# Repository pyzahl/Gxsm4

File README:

ATTENTION:

THIS IS A BETA VERSION AND WORK IN PROGRESS of Gxsm4 ported to GTK4.
See details of pending / not functional parts below in section 3.
(C) PyZahl 2021-12-31

1. General Information
======================

GXSM -- Gnome X Scanning Microscopy: A multi-channel image and
vector-probe data acquisition and visualization system designed for
SPM techniques (STM,AFM..), but also SPA-LEED. A plug-in interface
allows any user add-on data-processing and special hardware and
instrument support.

Based on several hardware options it supports a commercially available
DSP hardware and provided also Open Source Code for all the low level
signal processing tasks and instrument controls in a most flexible and
adaptable manner.

All latest stable software is available
via SVN (Gxsm4) and GIT (gxsm4-beta) only

or Live Demo/Install CD:
http://www.ventiotec.de/linux/GXSM-Linux.iso

GXSM Web Site: http://gxsm.sf.net

2. Installation
===============

Gxsm4 requires GTK4, GtkSourceView5, libfftw, libnetcdf, libquicktime, ...

Simple install procedure:

svn checkout svn+ssh://zahl@svn.code.sf.net/p/gxsm/svn/trunk/Gxsm4 Gxsm4-svn

./autogen.sh
make -j16 -k
sudo make install -j16 -k

Note: there may be compile errors as of incomplete porting progress.

See the file 'INSTALL' for more detailed information.

3. To-Do-List
=============
To be ported, recoded,pending or disfunctional features and comments:

We are also looking a new build system like MESON+Ninja for the future. But that later.

Simple things are pending or missing for currently not yet rewokred plugins, they simply fail to compile as of gtk4 changes, mainly those are:

gtk_widget_show_all(X)   --> removed completely from gtk4, replace with gtk_widget_show (X) and hope all others are shown.
                             Make sure every manually created widget is receiving it's gtk_show_widget().
			     Using the gxsm core "bp" builder tool it's all taken care of now!

gtk_container_add...     --> gtk_xxxwidget_set_child (GTK_XXXWIDGET (W), child)   (most the time a like)

gtk_entry_set/get_text() --> gtk_enter_buffer_set/get(gtk_entry_get_buffer (GTK_ENTRY (entry))) examples:
  gtk_entry_buffer_set_text (GTK_ENTRY_BUFFER (gtk_entry_get_buffer (GTK_ENTRY (g_object_get_data( G_OBJECT (as_control), "originalname"))))
  text = gtk_entry_buffer_get_text (GTK_ENTRY_BUFFER (gtk_entry_get_buffer (GTK_ENTRY (g_object_get_data (G_OBJECT (as_control), "basename"))))));

gtk_dialog_run()         --> no more -- see gapp_service.h for new examples and work arounds!

GTM_MENU... stuff        --> all is based on gtk_popover_... now, see core code for ported examples.

BUTTON signal names changed: the check/toggle button types and signals are changed and not mixable any more as separate objects.
                             watch for run time GTK WARNING messages regarding ignored signals!

Pending and known issues:
-------------------------

Window Position Management....  gtk4 does not provide any hands on that any more -- big convenience and usability issue 🙁
                                any one has an idea if select (particular gnome shell) have some handles to get around this???

File load vie Drag-n-Drop from filemanager: working, but currently only for single files. (new drap/drop controller)

"Kill" or close scan window is disfunctional... (only hiding): need to figure out how to fix. "window-delete" signals do not exist any more.... (removed from App-Init call) 🙁

Spin-Entry: Now shows the units again, but not always at startup (some defaut formatting), only after first touch... not yet sure why that is.

Profile: pending mouse actions for cursors... need to port to gtk_controller (easy), subtitle management, canvas window resizing is currently disfucntional.

DSP MOVER CONTROL BUTTONS: action signal problem of missing signal for "pressed". The "activate" does not do anything... I tried.
-?> Do I now need to add event controllers to the buttons (can I??) and all that stuff to do this?

All ENTRIES: added configuration menu option not yet attached and not accessible. Need to figure out how to add a custom menu entry to gtk_popovers.
             It is possible to manually edit the properties via the dconf-editor to get started.

DSP-CONTROL windows A, B -- initial TAB Drag to empty secondary window impossible (or hard??) to find a hook area to drop off. Work around for now:
Manually hack config via dconf-editor, then further DnD is easy and as usual again:

Set for example
/org/gnome/gxsm4/hwi/sranger-mk23/window-01-tabs = 'aclefghkmn------------------------------'
and
/org/gnome/gxsm4/hwi/sranger-mk23/window-02-tabs = 'dijo----------------------------'
Then start gxsm4 again.

FYI:
----
I disabled warning messages in configure.ac (CFLAG -w) to not get flooded by a silly issue I cannot fix and added -fpermissive.
This is needed as I get an error by the C++ compiler per default now when I xor  GTK_FLAGS  like A | B ... as this foces a typ conversion to int...
Oh well some crap.

much more ... to be figured out ans tested ....

4. How to report bugs
=====================

Bugs should be reported to the GNOME bug tracking system.
(http://bugzilla.gnome.org, product gedit). You will need to create an
account for yourself.

In the bug report please include:

* Information about your system. For instance:

   - What version of gxsm4
   - What operating system and version
   - What version of the gtk, glib and gnome libraries

  And anything else you think is relevant.

* How to reproduce the bug. 

* If the bug was a crash, the exact text that was printed out when the
  crash occurred.

* Further information such as stack traces may be useful, but is not
  necessary. If you do send a stack trace, and the error is an X error,
  it will be more useful if the stack trace is produced running the test
  program with the --sync command line option.

5. Patches
==========

Patches should also be submitted to bugzilla.gnome.org. If the patch
fixes an existing bug, add the patch as an attachment to that bug
report.

Otherwise, enter a new bug report that describes the patch, and attach
the patch to that bug report.

Please create patches with the git format-patch command.

If you are interested in helping us to develop gedit, please see the 
file 'AUTHOR' for contact information and/or send a message to the gedit
mailing list. See also the file 'HACKING' for more detailed information.

  The gxsm team.

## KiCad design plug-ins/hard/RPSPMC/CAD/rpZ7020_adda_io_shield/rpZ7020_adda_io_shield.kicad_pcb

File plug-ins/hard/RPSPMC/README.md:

# **ATTENTION:**

RedPitaya SPM-Control-PACPLL-Pulse Project

Experimental and development code only

(C) PyZahl 2025-01-05

# 1. General Information

GXSM -- Gnome X Scanning Microscopy: A multi-channel image and vector-probe data acquisition and visualization system designed for SPM techniques (STM,AFM..). A plug-in interface allows any user add-on data-processing and special hardware and instrument support.

This is a experimental complete all on one FPGA level SPM control.

All latest stable software is available now via GIT:
(Gxsm4 Beta currently) https://github.com/pyzahl/Gxsm4

or Live Demo/Install CD (with stable GXSM3):
http://www.ventiotec.de/linux/GXSM-Linux.iso

GXSM Web Site: http://gxsm.sf.net

# 4. A global design overview at Block and Interface Level:

# 5. NOTE:
We are currently discussing protective measures for our new hardware RPSPMC. Please contact us for details.

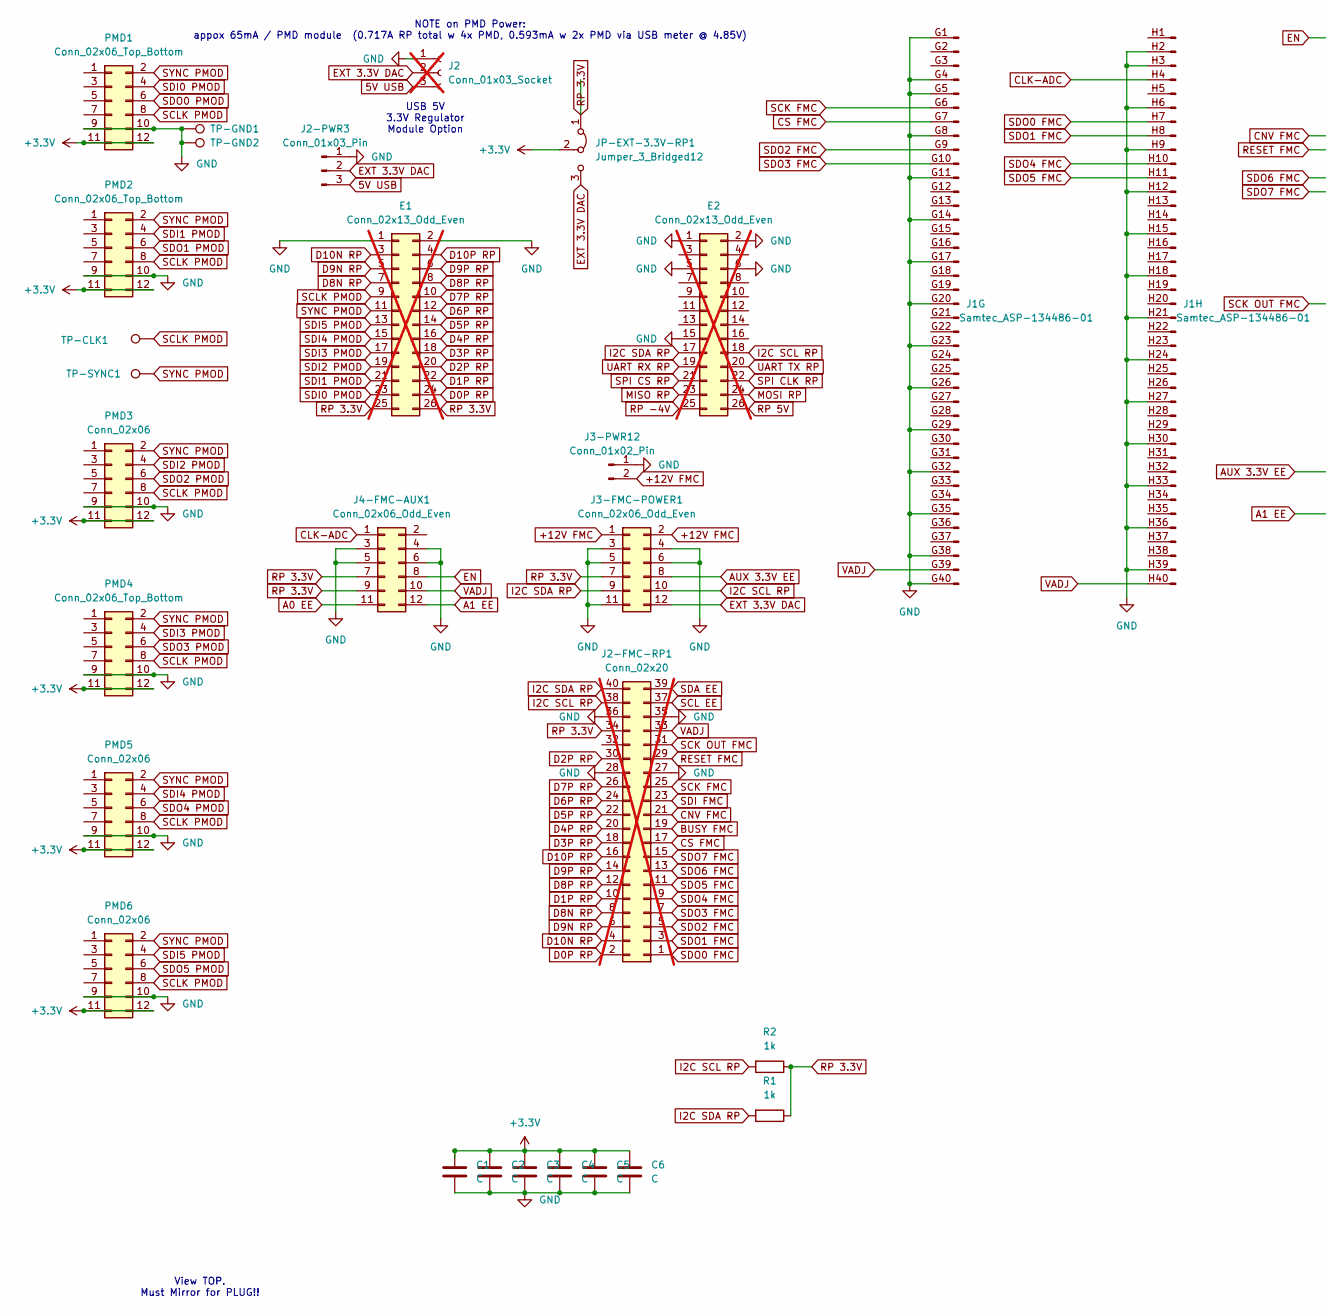
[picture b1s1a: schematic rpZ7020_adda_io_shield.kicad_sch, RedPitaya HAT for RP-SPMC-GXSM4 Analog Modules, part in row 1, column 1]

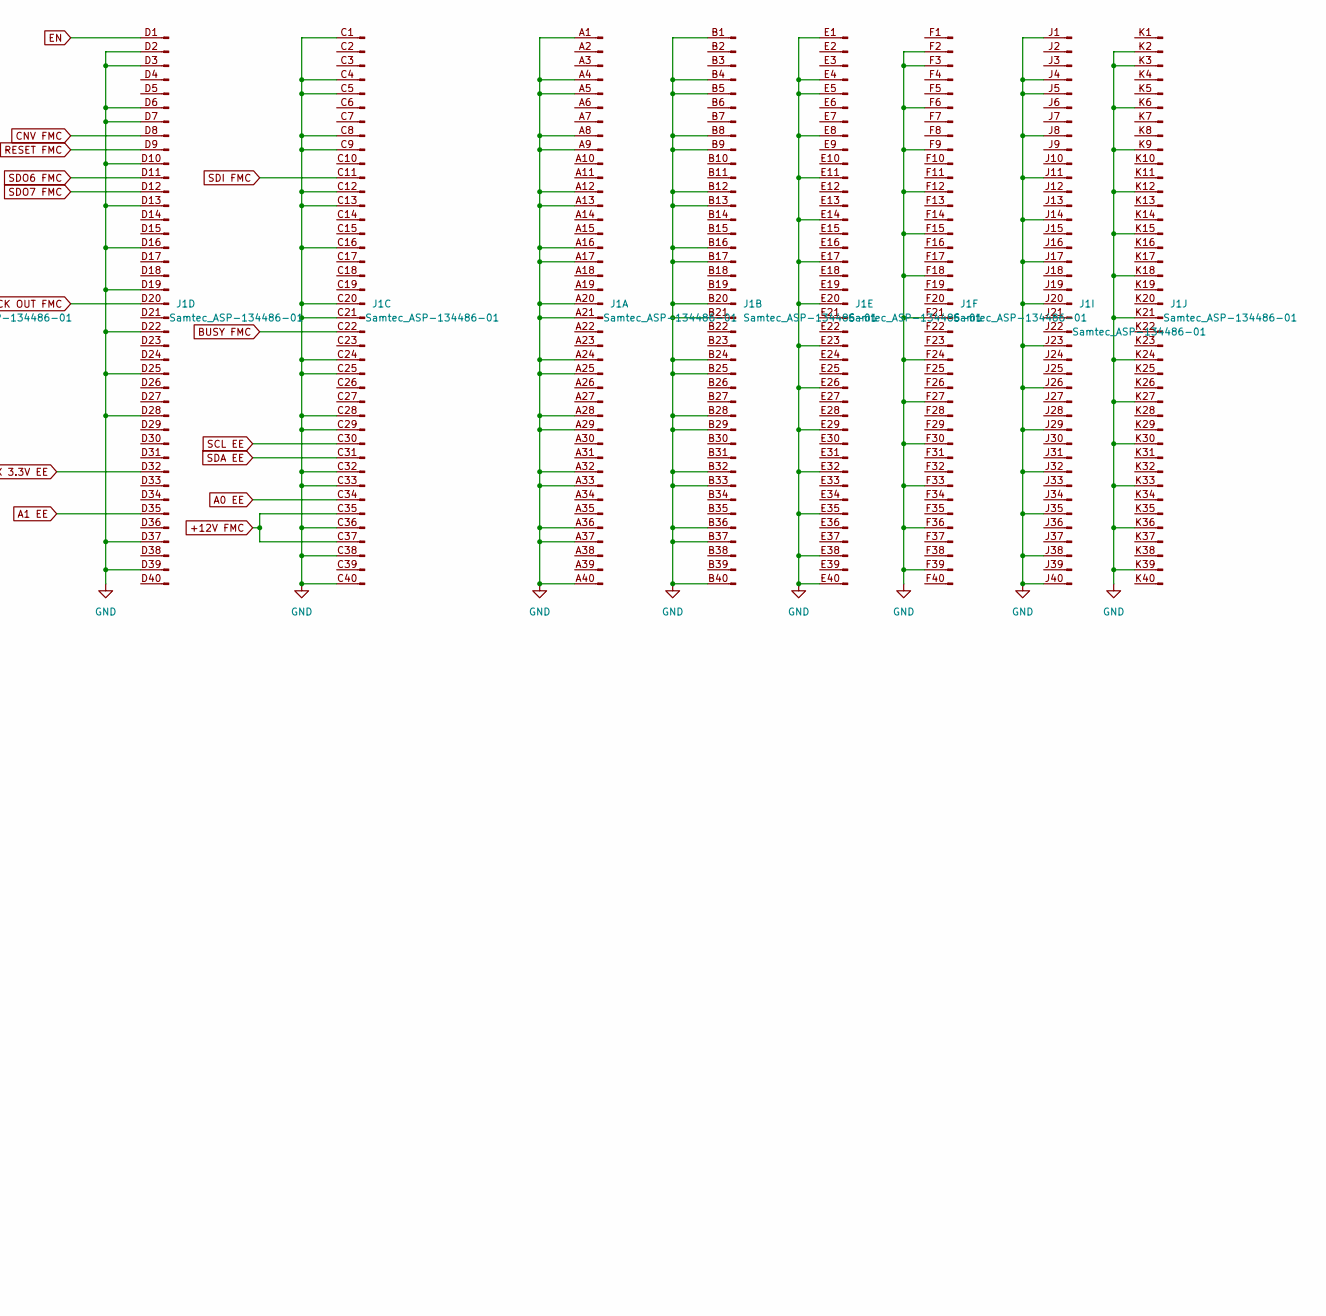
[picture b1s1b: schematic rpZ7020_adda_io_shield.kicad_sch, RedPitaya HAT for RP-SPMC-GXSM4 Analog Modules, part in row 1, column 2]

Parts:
C1, C2, C3, C4, C5, C6: C; C_1206_3216Metric_Pad1.33x1.80mm_HandSolder
E1, E2: Conn_02x13_Odd_Even; PinHeader_2x13_P2.54mm_Vertical; not fitted
J1: Samtec_ASP-134486-01; Samtec_FMC_ASP-134486-01_10x40_P1.27mm_Vertical
J2: Conn_01x03_Socket; PinSocket_1x03_P2.54mm_Vertical; not fitted
J2-FMC-RP1: Conn_02x20; PinHeader_2x20_P2.54mm_Vertical; not fitted
J2-PWR3: Conn_01x03_Pin; JST_PH_B3B-PH-K_1x03_P2.00mm_Vertical
J3-FMC-POWER1, J4-FMC-AUX1: Conn_02x06_Odd_Even; PinHeader_2x06_P2.54mm_Vertical
J3-PWR12: Conn_01x02_Pin; JST_PH_B2B-PH-K_1x02_P2.00mm_Vertical
JP-EXT-3.3V-RP1: Jumper_3_Bridged12; PinHeader_1x03_P2.54mm_Vertical
PMD1, PMD2, PMD4: Conn_02x06_Top_Bottom; PinSocket_2x06_P2.54mm_Vertical
PMD3, PMD5, PMD6: Conn_02x06; PinSocket_2x06_P2.54mm_Vertical
R1, R2: 1k; R_0805_2012Metric
TP-CLK1: TestPoint; Pin_D0.7mm_L6.5mm_W1.8mm_FlatFork
TP-GND1, TP-GND2: TestPoint; Pin_D0.7mm_L6.5mm_W1.8mm_FlatFork
TP-SYNC1: TestPoint; Pin_D0.7mm_L6.5mm_W1.8mm_FlatFork

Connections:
5V USB: J2.3, J2-PWR3.3
+3.3V: C1.2, C2.2, C3.2, C4.2, C5.2, C6.2, JP-EXT-3.3V-RP1.2 (C), PMD1.11, PMD1.12, PMD2.11, PMD2.12, PMD3.11, PMD3.12, PMD4.11, PMD4.12, PMD5.11, PMD5.12, PMD6.11, PMD6.12
+12V FMC: J1.C35 (Pin_35), J1.C37 (Pin_37), J3-FMC-POWER1.1, J3-FMC-POWER1.2, J3-PWR12.2
A0 EE: J1.C34 (Pin_34), J4-FMC-AUX1.11
A1 EE: J1.D35 (Pin_35), J4-FMC-AUX1.12
AUX 3.3V EE: J1.D32 (Pin_32), J3-FMC-POWER1.8
BUSY FMC: J1.C22 (Pin_22), J2-FMC-RP1.19
CLK-ADC: J1.H4 (Pin_4), J4-FMC-AUX1.1
CNV FMC: J1.D8 (Pin_8), J2-FMC-RP1.21
CS FMC: J1.G7 (Pin_7), J2-FMC-RP1.17
D0P RP: E1.24, J2-FMC-RP1.2
D1P RP: E1.22, J2-FMC-RP1.10
D2P RP: E1.20, J2-FMC-RP1.30
D3P RP: E1.18, J2-FMC-RP1.18
D4P RP: E1.16, J2-FMC-RP1.20
D5P RP: E1.14, J2-FMC-RP1.22
D6P RP: E1.12, J2-FMC-RP1.24
D7P RP: E1.10, J2-FMC-RP1.26
D8N RP: E1.7, J2-FMC-RP1.8
D8P RP: E1.8, J2-FMC-RP1.12
D9N RP: E1.5, J2-FMC-RP1.6
D9P RP: E1.6, J2-FMC-RP1.14
D10N RP: E1.3, J2-FMC-RP1.4
D10P RP: E1.4, J2-FMC-RP1.16
EN: J1.D1 (Pin_1), J4-FMC-AUX1.8
EXT 3.3V DAC: J2.2, J2-PWR3.2, J3-FMC-POWER1.12, JP-EXT-3.3V-RP1.3 (B)
GND: C1.1, C2.1, C3.1, C4.1, C5.1, C6.1, E1.1, E1.2, E2.1, E2.2, E2.5, E2.6, E2.15, J1.A1 (Pin_1), J1.A4 (Pin_4), J1.A5 (Pin_5), J1.A8 (Pin_8), J1.A9 (Pin_9), J1.A12 (Pin_12), J1.A13 (Pin_13), J1.A16 (Pin_16), J1.A17 (Pin_17), J1.A20 (Pin_20), J1.A21 (Pin_21), J1.A24 (Pin_24), J1.A25 (Pin_25), J1.A28 (Pin_28), J1.A29 (Pin_29), J1.A32 (Pin_32), J1.A33 (Pin_33), J1.A36 (Pin_36), J1.A37 (Pin_37), J1.A40 (Pin_40), J1.B1 (Pin_1), J1.B4 (Pin_4), J1.B5 (Pin_5), J1.B8 (Pin_8), J1.B9 (Pin_9), J1.B12 (Pin_12), J1.B13 (Pin_13), J1.B16 (Pin_16), J1.B17 (Pin_17), J1.B20 (Pin_20), J1.B21 (Pin_21), J1.B24 (Pin_24), J1.B25 (Pin_25), J1.B28 (Pin_28), J1.B29 (Pin_29), J1.B32 (Pin_32), J1.B33 (Pin_33), J1.B36 (Pin_36), J1.B37 (Pin_37), J1.B40 (Pin_40), J1.C1 (Pin_1), J1.C4 (Pin_4), J1.C5 (Pin_5), J1.C8 (Pin_8), J1.C9 (Pin_9), J1.C12 (Pin_12), J1.C13 (Pin_13), J1.C16 (Pin_16), J1.C20 (Pin_20), J1.C21 (Pin_21), J1.C24 (Pin_24), J1.C25 (Pin_25), J1.C28 (Pin_28), J1.C29 (Pin_29), J1.C32 (Pin_32), J1.C33 (Pin_33), J1.C36 (Pin_36), J1.C38 (Pin_38), J1.C40 (Pin_40), J1.D2 (Pin_2), J1.D3 (Pin_3), J1.D6 (Pin_6), J1.D7 (Pin_7), J1.D10 (Pin_10), J1.D13 (Pin_13), J1.D16 (Pin_16), J1.D19 (Pin_19), J1.D22 (Pin_22), J1.D25 (Pin_25), J1.D28 (Pin_28), J1.D37 (Pin_37), J1.D39 (Pin_39), J1.E1 (Pin_1), J1.E4 (Pin_4), J1.E5 (Pin_5), J1.E8 (Pin_8), J1.E11 (Pin_11), J1.E14 (Pin_14), J1.E17 (Pin_17), J1.E20 (Pin_20), J1.E23 (Pin_23), J1.E26 (Pin_26), J1.E29 (Pin_29), J1.E32 (Pin_32), J1.E35 (Pin_35), J1.E38 (Pin_38), J1.E40 (Pin_40), J1.F2 (Pin_2), J1.F3 (Pin_3), J1.F6 (Pin_6), J1.F9 (Pin_9), J1.F12 (Pin_12), J1.F15 (Pin_15), J1.F18 (Pin_18), J1.F21 (Pin_21), J1.F24 (Pin_24), J1.F27 (Pin_27), J1.F30 (Pin_30), J1.F33 (Pin_33), J1.F36 (Pin_36), J1.F39 (Pin_39), J1.G1 (Pin_1), J1.G4 (Pin_4), J1.G5 (Pin_5), J1.G8 (Pin_8), J1.G11 (Pin_11), J1.G14 (Pin_14), J1.G17 (Pin_17), J1.G20 (Pin_20), J1.G23 (Pin_23), J1.G26 (Pin_26), J1.G29 (Pin_29), J1.G32 (Pin_32), J1.G35 (Pin_35), J1.G38 (Pin_38), J1.G40 (Pin_40), J1.H2 (Pin_2), J1.H3 (Pin_3), J1.H6 (Pin_6), J1.H9 (Pin_9), J1.H12 (Pin_12), J1.H15 (Pin_15), J1.H18 (Pin_18), J1.H21 (Pin_21), J1.H24 (Pin_24), J1.H27 (Pin_27), J1.H30 (Pin_30), J1.H33 (Pin_33), J1.H36 (Pin_36), J1.H39 (Pin_39), J1.J1 (Pin_1), J1.J4 (Pin_4), J1.J5 (Pin_5), J1.J8 (Pin_8), J1.J11 (Pin_11), J1.J14 (Pin_14), J1.J17 (Pin_17), J1.J20 (Pin_20), J1.J23 (Pin_23), J1.J26 (Pin_26), J1.J29 (Pin_29), J1.J32 (Pin_32), J1.J35 (Pin_35), J1.J38 (Pin_38), J1.J40 (Pin_40), J1.K2 (Pin_2), J1.K3 (Pin_3), J1.K6 (Pin_6), J1.K9 (Pin_9), J1.K12 (Pin_12), J1.K15 (Pin_15), J1.K18 (Pin_18), J1.K21 (Pin_21), J1.K24 (Pin_24), J1.K27 (Pin_27), J1.K30 (Pin_30), J1.K33 (Pin_33), J1.K36 (Pin_36), J1.K39 (Pin_39), J2.1, J2-FMC-RP1.27, J2-FMC-RP1.28, J2-FMC-RP1.35, J2-FMC-RP1.36, J2-PWR3.1, J3-FMC-POWER1.3, J3-FMC-POWER1.4, J3-FMC-POWER1.5, J3-FMC-POWER1.6, J3-FMC-POWER1.11, J3-PWR12.1, J4-FMC-AUX1.3, J4-FMC-AUX1.4, J4-FMC-AUX1.5, J4-FMC-AUX1.6, PMD1.9, PMD1.10, PMD2.9, PMD2.10, PMD3.9, PMD3.10, PMD4.9, PMD4.10, PMD5.9, PMD5.10, PMD6.9, PMD6.10, TP-GND1.1, TP-GND2.1
I2C SCL RP: E2.18, J2-FMC-RP1.38, J3-FMC-POWER1.10, R2.2
I2C SDA RP: E2.17, J2-FMC-RP1.40, J3-FMC-POWER1.9, R1.2
MISO RP: E2.23
MOSI RP: E2.24
RESET FMC: J1.D9 (Pin_9), J2-FMC-RP1.29
RP 3.3V: E1.25, E1.26, J2-FMC-RP1.34, J3-FMC-POWER1.7, J4-FMC-AUX1.7, J4-FMC-AUX1.9, JP-EXT-3.3V-RP1.1 (A), R1.1, R2.1
RP 5V: E2.26
RP -4V: E2.25
SCK FMC: J1.G6 (Pin_6), J2-FMC-RP1.25
SCK OUT FMC: J1.D20 (Pin_20), J2-FMC-RP1.31
SCL EE: J1.C30 (Pin_30), J2-FMC-RP1.37
SCLK PMOD: E1.9, PMD1.8, PMD2.8, PMD3.8, PMD4.8, PMD5.8, PMD6.8, TP-CLK1.1; also elsewhere on the board
SDA EE: J1.C31 (Pin_31), J2-FMC-RP1.39
SDI0 PMOD: E1.23, PMD1.4
SDI1 PMOD: E1.21, PMD2.4
SDI2 PMOD: E1.19, PMD3.4
SDI3 PMOD: E1.17, PMD4.4
SDI4 PMOD: E1.15, PMD5.4
SDI5 PMOD: E1.13, PMD6.4
SDI FMC: J1.C11 (Pin_11), J2-FMC-RP1.23
SDO0 FMC: J1.H7 (Pin_7), J2-FMC-RP1.1
SDO0 PMOD: PMD1.6
SDO1 FMC: J1.H8 (Pin_8), J2-FMC-RP1.3
SDO1 PMOD: PMD2.6
SDO2 FMC: J1.G9 (Pin_9), J2-FMC-RP1.5
SDO2 PMOD: PMD3.6
SDO3 FMC: J1.G10 (Pin_10), J2-FMC-RP1.7
SDO3 PMOD: PMD4.6
SDO4 FMC: J1.H10 (Pin_10), J2-FMC-RP1.9
SDO4 PMOD: PMD5.6
SDO5 FMC: J1.H11 (Pin_11), J2-FMC-RP1.11
SDO5 PMOD: PMD6.6
SDO6 FMC: J1.D11 (Pin_11), J2-FMC-RP1.13
SDO7 FMC: J1.D12 (Pin_12), J2-FMC-RP1.15
SPI CLK RP: E2.22
SPI CS RP: E2.21
SYNC PMOD: E1.11, PMD1.2, PMD2.2, PMD3.2, PMD4.2, PMD5.2, PMD6.2, TP-SYNC1.1; also elsewhere on the board
UART RX RP: E2.19
UART TX RP: E2.20
VADJ: J1.G39 (Pin_39), J1.H40 (Pin_40), J2-FMC-RP1.33, J4-FMC-AUX1.10

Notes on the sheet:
USB 5V 3.3V Regulator Module Option
View TOP. Must Mirror for PLUG!!
NOTE on PMD Power: appox 65mA / PMD module (0.717A RP total w 4x PMD, 0.593mA w 2x PMD via USB meter @ 4.85V)

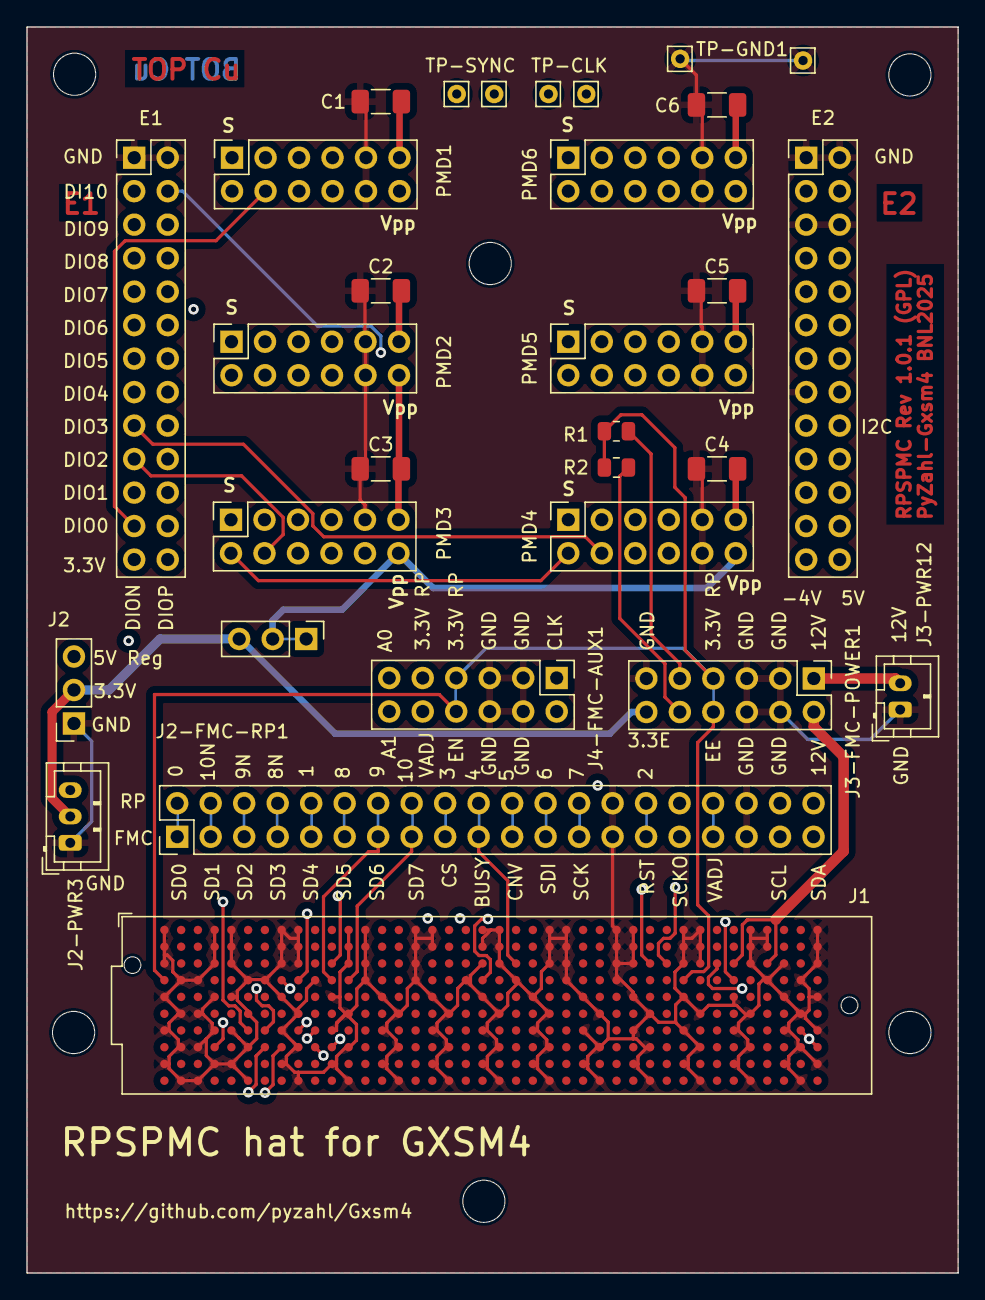
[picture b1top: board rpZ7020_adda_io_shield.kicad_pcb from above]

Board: 4 copper layers, 70.6 x 94.5 mm, 36 parts (0 on the bottom side), 53 nets.

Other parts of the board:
MH1, MH2, MH3, MH4, MH5, MH6: MountingHole_3.2mm_M3
TP-CLK: TestPoint; Pin_D0.7mm_L6.5mm_W1.8mm_FlatFork
TP-SYNC: TestPoint; Pin_D0.7mm_L6.5mm_W1.8mm_FlatFork

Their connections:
SCLK PMOD: TP-CLK.1; also elsewhere on the board
SYNC PMOD: TP-SYNC.1; also elsewhere on the board

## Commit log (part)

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2025-05-09 added new template action scripts
2025-05-12 fixed createc HV5 app channel order/entry and defaults patched vec scan gen to select XY for init pos auto dxy calc enable after changes/separating
2025-05-12 changed file
2025-05-20 fixed GVP am/fm store typo
2025-05-21 reorganizing graphs matrix, scaled GVP-FM to Hz
2025-05-21 Delete plug-ins/hard/RPSPMC directory
    Moved into separate repository
2025-05-24 added layerinfo data update to core. New: Auto unit prefix adj.
2025-05-24 rearrange time-mon channel. Fixed time-mon scan source.
2025-05-25 added accels for view zoom
2025-05-27 separated Z-Pos into Z-Servo + Slope components in display
2025-05-31 work on BQ
2025-06-01 pyremote cleanups and added auto restore of last opened/saved file
2025-06-05 added/adjusted SRCS MUX mapping ** WARNING, REQUIRES FPGA UPDATE V >= 20250603
2025-06-05 added probe event data access to pyremote
2025-06-08 enabled time mon always for GVP (tmp solution)
2025-06-09 added bin display to px coord mode
2025-06-09 RTQ json access
2025-06-10 python RTcontrol access to JSON HW
2025-06-12 added GVP checks
2025-06-13 adding check and Q dialog to GVP star twhen busy otherwise and a forced extra GVP stop w delay
2025-06-14 work on pending gtk4 and port issues
2025-06-15 corrected z-polarity management inconsitencies.
2025-06-17 tweaks to meters
2025-06-17 added vu-meter frame template
2025-06-23 work on lockin+bq's
2025-06-28 adjusted FIR settings
2025-07-03 work on vpdata file v0.03 support for read back added auto skip vpfile counter if existing to prevent over write
2025-07-03 work on gtk4 port completion for vp data viewer
2025-07-07 fixed scale tic marks drawing at startups and corrected init scale pos if log
2025-07-22 implemented PF trigger source
2025-08-02 Update changelog
2025-08-21 added v and t support for pyremote getslice added get_instrument_gains_xyz
2025-08-21 fixed create scan from np with layers
2025-08-22 fixed gain types in pyobj
2025-08-22 added gxsm4 pyremote script collection
2025-08-25 patch and fix for rpspmc gvp vpdata XY-Scan write and auto recovery if missing from HDR
2025-08-25 work in analysis script
2025-08-27 added z-probe fit for exact z eval
2025-08-28 work on script
2025-08-29 fixed auto detection of drift corr for multi dim copy and copy scan
2025-08-29 added CSS name for gtk sourec file view pyremote and adjusted default font size to 16
2025-08-29 implemented 2D interpolation modes up to bilinea/bicubic for Zdata
2025-09-03 view control drife correction: rework with correct units
2025-09-04 put view label tab css to rot=0, gtl4 wiget allocation for rotated is wrong
2025-09-05 fix OSD pos when not in QF=1
2025-09-07 added user event logging for basic parameters while scanning
2025-09-07 auto setup pyremote panes positions
2025-09-09 work on map analysis
2025-09-09 work on mol bg options
2025-09-18 optimized remotepy quick call toolbar
2025-09-29 added VECX info to logging, improved formatting
2025-09-29 fixed init of history list
2025-09-30 updates: Lck Sens ID, Filter Script auto Fc calc., added PC Jmp dest info to log
2025-09-30 added/included nctopng to meson build and thumbnailing setup to install
2025-10-01 added desktop entry for Gxsm4
2025-10-08 added windowtitile always
2025-10-08 added gxsm window geom to hypr config tool
2025-10-08 added hypr gxsm4 config defaults
2025-10-09 added hyprland support for geometry management
2025-10-10 added hypr rule
2025-10-14 work on monitors
2025-10-16 work on porting thumbnailer to nc4 as a test case
2025-10-16 new netcdf lib based thumbnailer
2025-10-17 update on version message
2025-10-20 better verbosity for error handling
2025-10-20 added thumbnailter test script
2025-10-20 thumbnailer usage info update
2025-10-23 porting to NC4
2025-10-23 it compiles and links now...
2025-10-23 compiling and start working with hiccups...
2025-10-23 basic test NC4 reads/write OK. Also Gxsm3 can still open rewritten files -- so far. Future addition may make use of NC4 features. TBD.
2025-10-23 replaced old nctopng.cpp with new nc4topng.cpp version, nc4topng.cpp scheduled for removal. rempoved all obsoleted legacy netcdf deps.
2025-10-24 fixed reading value lookup
2025-10-24 work on ncview tab
2025-10-25 NcView tab works, improved with unit management as available i natributes
2025-10-25 fixing details w user-events
2025-10-26 fixed catching of missing/checking for attribs added improoved error/info handling and reporting
2025-10-26 cleanups
2025-11-03 work on lck and bq and ZS-bq-notch
2025-11-04 work on bq config
2025-11-05 work on Lck/BQ
2025-11-05 updates to LCK decii calc, added IV exec button
2025-11-08 added sim modes
2025-11-10 cleanups of filter calc + sim script
2025-11-11 cleanups. rpspmc scale data to unit for swp set to one as scales to unit at transfer time.
2025-11-12 added LCK gain info + auto unit/scale for display
2025-11-14 adjusted BQ deci to 16 fixed
2025-11-14 added filter conf/test script
2025-11-14 sym IIR for profile
2025-11-15 added vpdata plot demo
2025-11-17 clenaups of recscources, default adjustments for filters
2025-11-17 added section colors -- exp.
2025-11-17 updated BQ/IIR compute script
2025-11-18 fixed colored sections
2025-11-20 changed scan data to always been placed in normal x-forward direction. For X+ and X- scan dir. Pending patch/check for MK23 wha tis still experimental for gxsm4 anyways.
2025-11-20 added units and att to XYV lookups
2025-11-23 cleanups dataio updating xsminfo about device auto init filter section on cold start
2025-11-23 fixed typo
2025-11-24 cleanups, added missing rpspmc_hwi basic nc params
2025-11-24 added stream info to gxsm main log
2025-11-25 updated unit translations
2025-12-08 Debian packaging: Ubuntu 25.10
    * separate gxsm4 and gxsm-nc-thumbnaile
    * created control file for Ubuntu 25.10 (which can run hypr)
2025-12-08 Addes missing json-dependency
2025-12-11 added info post store
2025-12-15 added silent pyremote hook to call .gxsm4/pyactions/auto-save-chNN.py at auto save for every selected scan source channel.
2025-12-16 start adding LCK parameters from GUI renamed HwI JSON data prefixes for ncf
2025-12-18 clenaups of PanView
2025-12-23 adjusted color of scan org mark
2025-12-24 added gradient fill to cairo_item_circle
2026-01-04 added dpulse data to update job
2026-01-06 added SHM block GXSM ACTIONs for gxsm.set/get
2026-01-07 added docu/comments
2026-01-08 patched missed var rename
2026-01-08 work on lib
2026-01-08 tested gxsm4process lib OK afer few patches
2026-01-09 separated monitoring and action SHM serving. monitor data update as it comes in action requests are checked on a timer basis unrelated: added clean plugin unload to gxsm quit
2026-01-09 cleanups ported CreatecHV amp monitorign to new SHM gxsm support lib
2026-01-12 work on generic pyremote shm bridge ** WARNING: experimental
2026-01-12 work on PySHM, looking good. Needs testing and method impl in lib.
2026-01-13 added example for extern vpdata plot
2026-01-13 code cleanups
2026-01-14 cleanups and removal of obsoleted testing SHM action from RPSPMC monitors
2026-01-14 EXPERIMENTAL: implemented on-the-fly IVC gain settings
2026-01-15 testing IVC live gain switching, few patches. Added IVC gain indicator to PanView along with a few formatting improvements
2026-01-15 added auto freeze of various gain setting while scanning and more cleanups
2026-01-15 tested script for RP scope data fetch
2026-01-16 testing scope data xfer to python
2026-01-20 WARNING: EXPERIMENTAL NEW HIGH SPEED MONITOR DATA STREAMING ADDED
2026-01-21 cleanups, added history push and use of fast XYZ,I,dF for RTQuery
2026-01-22 allowing ProbeHUD window to be resized
2026-01-22 added signal selectors to ProbeHUD
2026-01-23 work on ProbeHUD KAO fxied limiting conversion for variable gain
2026-01-24 work on micro KAO
2026-01-25 finished ProbeHUB overhaul with all new 4CH KAO
2026-01-26 patched top ProbeHUD KAO, cleanups, moved to all double precison.
2026-01-26 added demo scripts and added/adjusted gxsm.scanwait
2026-01-27 critical patch: fixed auto-save while scan update
2026-01-27 removed tmp xyz gain scale *20
2026-01-28 back patched failed attempt to make DnD work in Hyrp
2026-01-28 added enevlop trace mode
2026-01-30 added warning highlighening for Bias and Z-Pos together with GVP-U ans GVP-Z Monitors of any significant GVP residual offsets are presnet. Normal to get highlighted (Blinking red) when GVP in action 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
2026-01-30 KAO tweaks
2026-02-02 added default window title as optional arg to AppBase class
2026-02-02 added servo to rt_query_rpspmc
2026-02-03 added experimenta script for Robin
2026-02-03 few more tweaks
2026-03-13 fixed remote action -- uninitialized varible in case of optional argument.
2026-03-16 patch: added ra -> data_length=0 init to action setups
2026-03-17 updated remote_action_cb struct to class for better data inegrity
2026-03-17 major rework of left behind old style remote hooks -- this hopefully finally adresses the issue. This commit includes experimental new FPGA feature support NOT yet main stream related to ultra fast d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
2026-03-22 fixed ref component gen and STS slope of section dual
2026-03-23 added Y-extra scale mode
2026-04-05 removed ancient DataAq Preferences and HW assignment schemes added new DataSource management to Channel-Selctor and new DataSource description class. To be populated via HwI using main_get_gapp()->ch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
2026-04-05 fixed time-mon assignments
2026-04-10 updated/fixed sim HwI
2026-04-10 added up to 3 channel support in 11,12,13 -> ch1,2,3 (aka Topo, Curr, dFreq)
2026-04-20 work on HS data
2026-04-22 added TESTPOINT msg for potential tricky seg fault in case of python/numpy version clash/Venv use. As confusing issue if unknown cause. Can not catch this simply.
2026-04-28 Preparing first release on Ubuntu26.04LTS * removed doubled desktop menu entry * removed obsolete links to ventiotec.com in context menu * added links to sf.net and github.com in context menu * rewor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
2026-05-04 updates/added hypr gxsm default configs
2026-05-06 added MOVE option to drop_traget to make DnD work with Hypr
2026-06-03 Add local microscope copilot baseline
2026-06-03 Update GVP save restore and VP data helper
2026-06-03 Add Gradio microscope copilot GUI skeleton
2026-06-04 Move control policy to GUI tab
2026-06-04 Prevent chat from claiming hardware actions
2026-06-04 Include scan slope settings in readback
2026-06-04 Handle chat bias readback deterministically
2026-06-04 Generalize chat parameter readback and safe writes
2026-06-04 Route chat tip analysis to deterministic scan assessment
2026-06-04 Enhance local microscope copilot controls
2026-06-04 Fix tip planner move readiness and coordinates
2026-06-04 Improve tip planner hazards and chat intents
2026-06-04 Add long GVP wait and stop control
2026-06-05 Improve chat units and scan analysis
2026-06-05 Allow unitless scan point counts
2026-06-05 Improve chat offset controls
2026-06-05 Externalize copilot configuration
2026-06-05 Add tip position overlays and handoff memory
2026-06-05 Fix live XY monitor scaling and hazard mapping
2026-06-05 Harden PySHM access and planner refresh coordination
2026-06-05 Ignore transient scan-line artifacts as hazards
2026-06-06 Refine microscope copilot README introduction
2026-06-07 Wayland WM hack
2026-06-07 Wayland WM hack for Gxsm Window Management
2026-06-07 fixed css template
2026-06-08 added GETCHECK fucntion, 16M SHM
2026-06-08 added missing catch for non exisiting data request in getslice
2026-06-10 fixed slow to V/s conversion for manual tip move
2026-06-13 patch for time conversion signum issue (>15s aka > 32bit)
2026-06-13 experimental patch for focus inconsistencyies
2026-06-14 clean-ups / moved messages into DBG LVL macros removed obsoleted gtk_widget_show() calls work in bulletproofing gxsm-wm-extension
2026-06-15 fixed app_profile, remoevd one too many gtk_widget_show/ missed to replace with window present
2026-06-15 adjusting window placement attempt delay
2026-06-15 debugging frozen window issue in Wayland after loading multiple images
2026-06-15 added auto-hide flase to popopvre message
2026-06-16 work on Wayland window management
2026-06-17 added broken wayland RDP workaround to auto move window to first screen/X below... remoevd arror from progress popover
2026-06-18 adjusting bins for auto contrast/scale
2026-06-18 added SHM init/management skipping when stareted as secondary instance via gxsm4 -s
2026-06-19 fine tuning gxsm-wm, auto managing multi gxsm intances on different workspaces
2026-06-19 added NULL check in match in case if win... returns Null
2026-06-19 Fix typo in README for SHM bridge
2026-06-19 major code base cleanup and maintenance fixed file load from command line

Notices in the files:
plug-ins/hard/RPSPMC/CAD/rpZ7020_adda_io_shield/rpZ7020_adda_io_shield.kicad_pcb:
RPSPMC Rev 1.0.1 (GPL)
